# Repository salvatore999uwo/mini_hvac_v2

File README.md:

# mini_hvac_v2
Second version of the temperature control system for a small model room.

Photos:
As shown below, this version is made from three parts: Wooden structure, electronic boards, and thermal transfer area. 
The wooden structure is made up of a plywood base and a model room built from studs. There will be a drywall covering over the stud room to simulate a real temperature-controlled room.
The electronic boards are simply the PCB and the power supply for the project. There will be several wires running between the boards and the thermal transfer area.
The thermal transfer area is shown by the heatsinks and fans on the picture below. This area is composed of the TEC module, which creates a large temperature difference, and the heatsinks and fans that allow the TEC module to move thermal energy out of or into the room.

Current PCB 3D Model:

One schematic page i've been working on:

Current PCB Design:

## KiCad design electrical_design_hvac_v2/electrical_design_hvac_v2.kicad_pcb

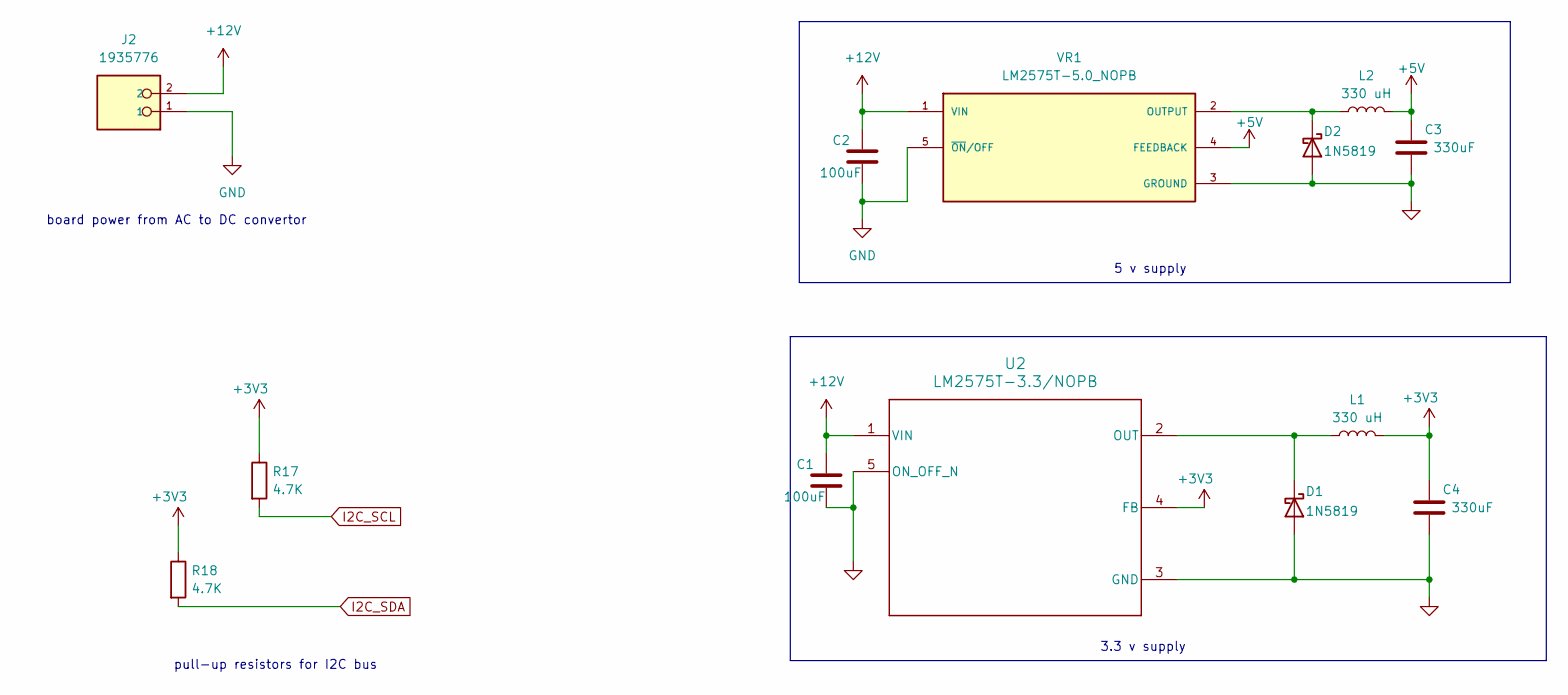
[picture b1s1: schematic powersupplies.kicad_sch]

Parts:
C1, C2: 100uF; C_1210_3225Metric_Pad1.33x2.70mm_HandSolder
C3, C4: 330uF; C_1210_3225Metric_Pad1.33x2.70mm_HandSolder
D1, D2: 1N5819; D_DO-41_SOD81_P10.16mm_Horizontal
J2: 1935776; PHOENIX_1935776; PARTREV 19.10.2016
L1, L2: 330 uH; IND_1210-WE-PD_WRE
R17, R18: 4.7K; R_1210_3225Metric_Pad1.30x2.65mm_HandSolder
U2: LM2575T-3.3/NOPB; KC0005A
VR1: LM2575T-5.0_NOPB; KC0005A; PARTREV E

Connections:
+5V: C3.1, L2.2, VR1.4 (FEEDBACK); also elsewhere on the board
+12V: C1.1, C2.1, J2.2, U2.1 (VIN), VR1.1 (VIN); also elsewhere on the board
GND: C1.2, C2.2, C3.2, C4.2, D1.2 (A), D2.2 (A), J2.1, U2.3 (GND), U2.5 (ON_OFF_N), VR1.3 (GROUND), VR1.5 (~ON/OFF); also elsewhere on the board
I2C_SCL: R17.2; also elsewhere on the board
I2C_SDA: R18.2; also elsewhere on the board
unnamed: D1.1 (K), L1.1, U2.2 (OUT)
unnamed: D2.1 (K), L2.1, VR1.2 (OUTPUT)

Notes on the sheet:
5 v supply
board power from AC to DC convertor
pull-up resistors for I2C bus
3.3 v supply

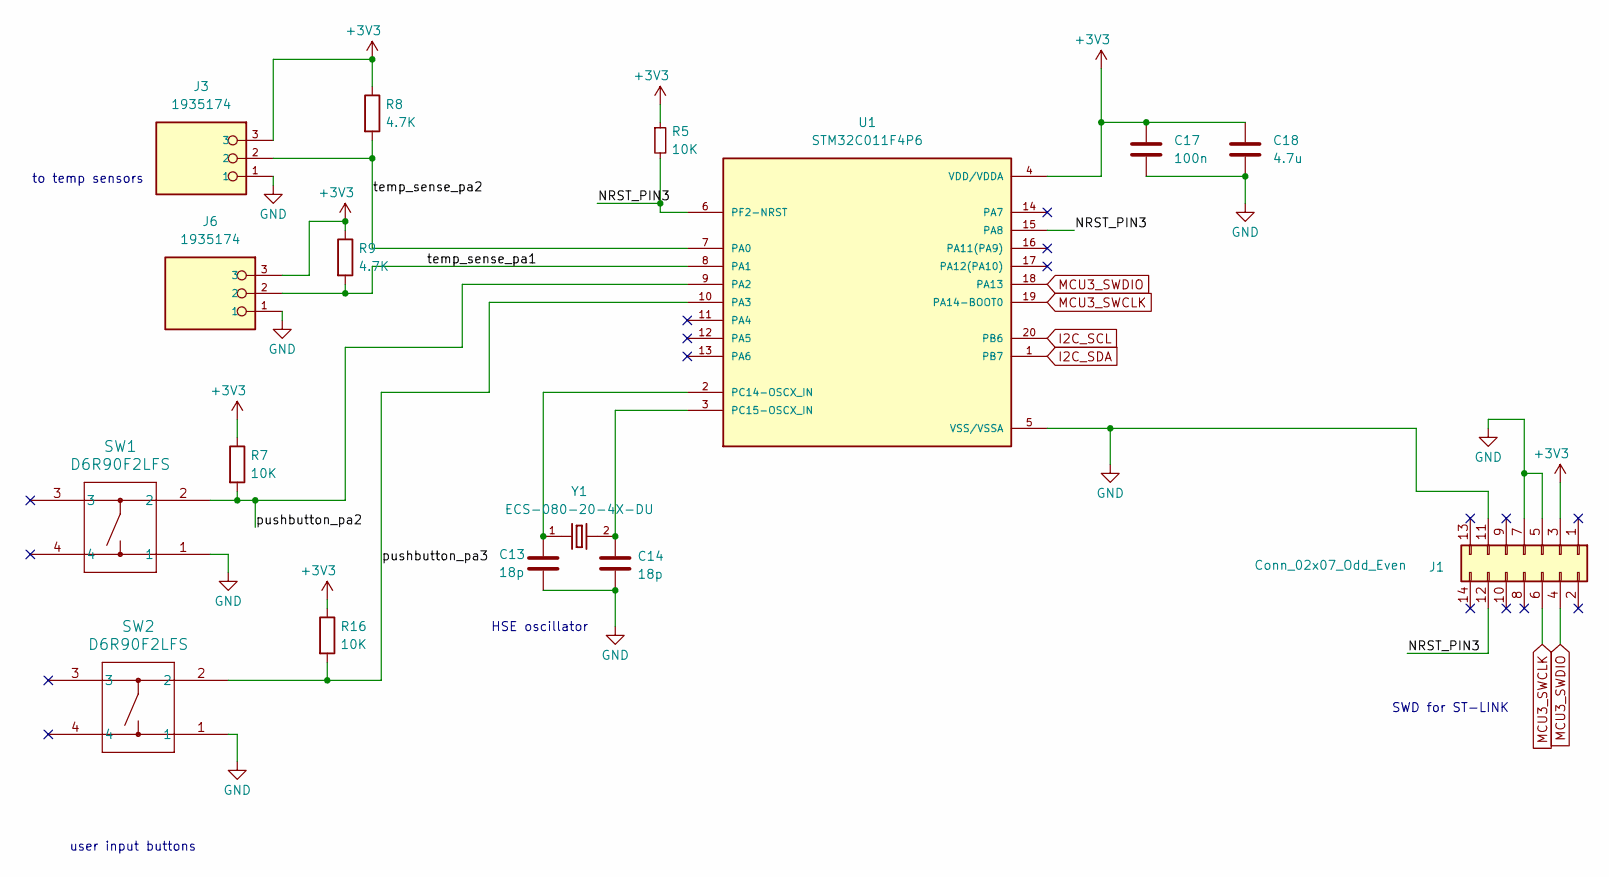
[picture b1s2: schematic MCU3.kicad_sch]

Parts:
C13, C14: 18p; C_1210_3225Metric_Pad1.33x2.70mm_HandSolder
C17: 100n; C_1210_3225Metric_Pad1.33x2.70mm_HandSolder
C18: 4.7u; C_1210_3225Metric_Pad1.33x2.70mm_HandSolder
J1: Conn_02x07_Odd_Even; PinHeader_2x07_P1.27mm_Vertical
J3, J6: 1935174; PHOENIX_1935174
R5, R7, R16: 10K; R_1210_3225Metric_Pad1.30x2.65mm_HandSolder
R8, R9: 4.7K; R_1210_3225Metric_Pad1.30x2.65mm_HandSolder
SW1, SW2: D6R90F2LFS; D6R90_CNK
U1: STM32C011F4P6; SOP65P640X120-20N; PARTREV 3
Y1: ECS-080-20-4X-DU; XTAL_ECS-160-20-4X

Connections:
/MCU3/NRST_PIN3: J1.12, R5.2, U1.6 (PF2-NRST), U1.15 (PA8)
/MCU3/pushbutton_pa2: R7.2, SW1.2, U1.9 (PA2)
/MCU3/pushbutton_pa3: R16.2, SW2.2, U1.10 (PA3)
/MCU3/temp_sense_pa1: J6.2, R9.2, U1.8 (PA1)
/MCU3/temp_sense_pa2: J3.2, R8.2, U1.7 (PA0)
GND: C13.2, C14.2, C17.2, C18.2, J1.5, J1.7, J1.11, J3.1, J6.1, SW1.1, SW2.1, U1.5 (VSS/VSSA); also elsewhere on the board
I2C_SCL: U1.20 (PB6); also elsewhere on the board
I2C_SDA: U1.1 (PB7); also elsewhere on the board
MCU3_SWCLK: J1.6, U1.19 (PA14-BOOT0)
MCU3_SWDIO: J1.4, U1.18 (PA13)
unnamed: C13.1, U1.2 (PC14-OSCX_IN), Y1.1
unnamed: C14.1, U1.3 (PC15-OSCX_IN), Y1.2

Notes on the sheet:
HSE oscillator
user input buttons
SWD for ST-LINK
to temp sensors

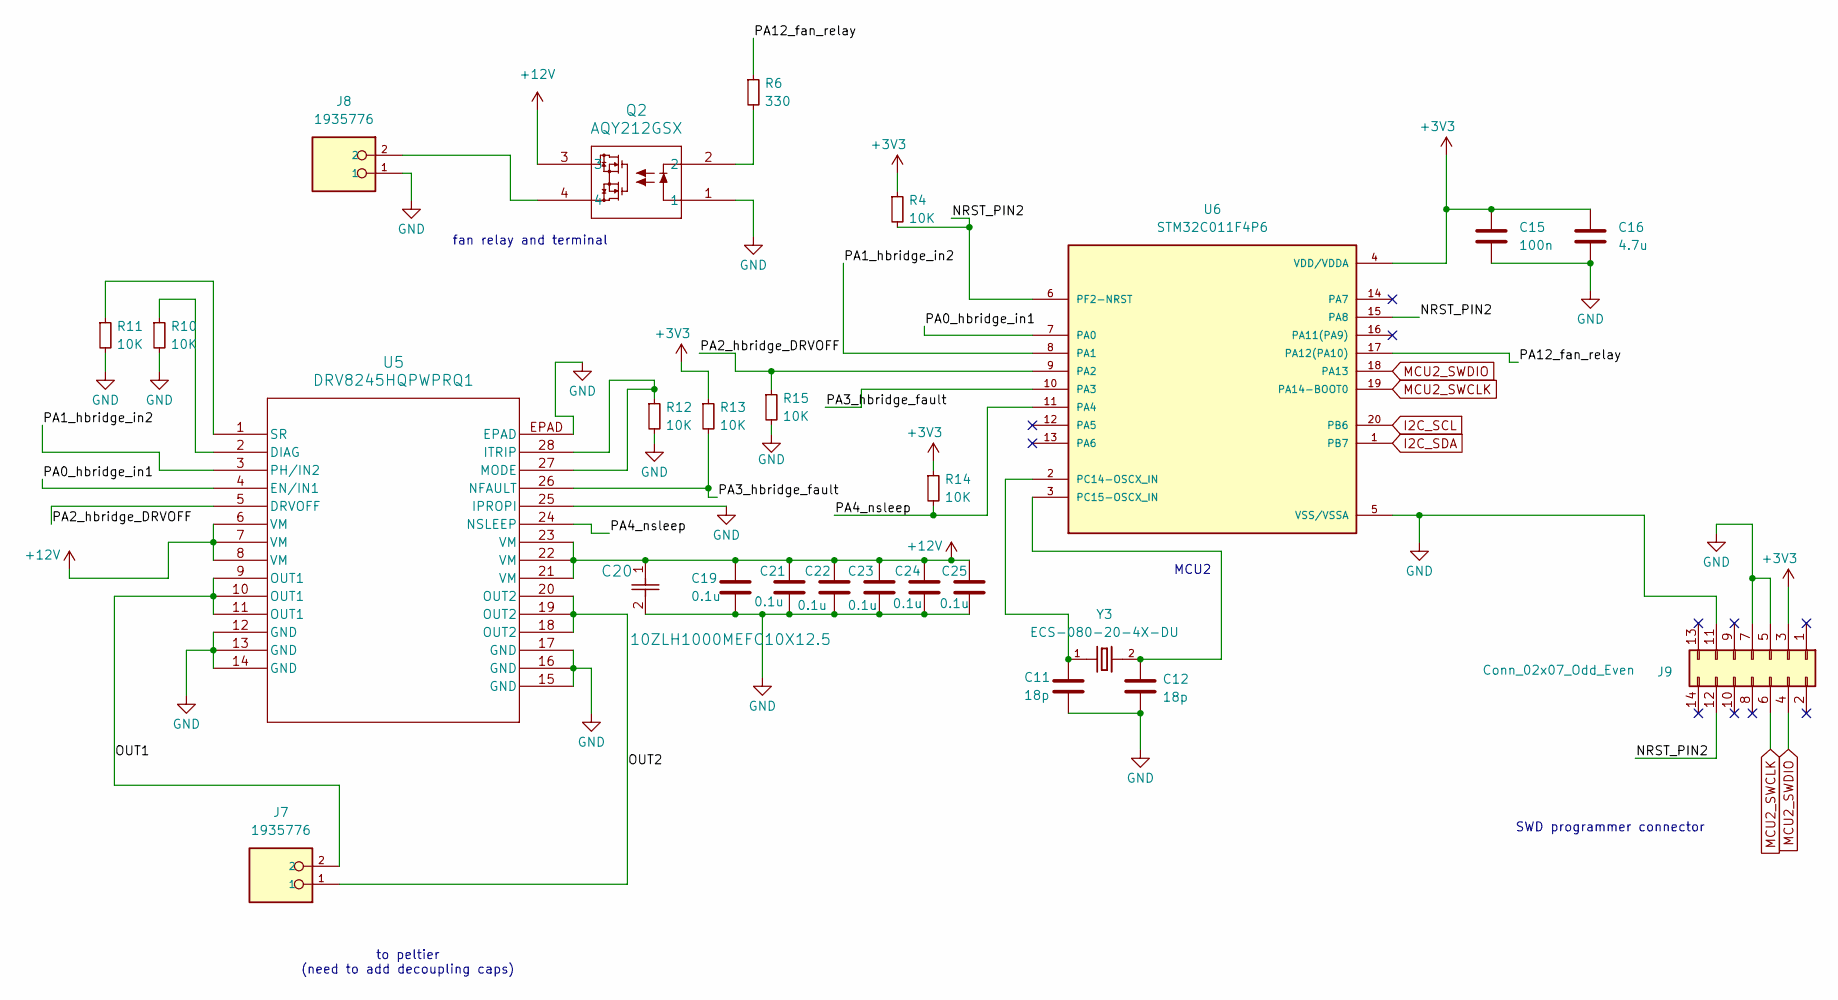
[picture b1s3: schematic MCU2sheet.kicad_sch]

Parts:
C11, C12: 18p; C_1210_3225Metric_Pad1.33x2.70mm_HandSolder
C15: 100n; C_1210_3225Metric_Pad1.33x2.70mm_HandSolder
C16: 4.7u; C_1210_3225Metric_Pad1.33x2.70mm_HandSolder
C19, C21, C22, C23, C24, C25: 0.1u; C_1210_3225Metric_Pad1.33x2.70mm_HandSolder
C20: 10ZLH1000MEFC10X12.5; CAP_10X12.5_RUB
J7, J8: 1935776; PHOENIX_1935776; PARTREV 19.10.2016
J9: Conn_02x07_Odd_Even; PinHeader_2x07_P1.27mm_Vertical
Q2: AQY212GSX; SOP4_PAN
R4, R10, R11, R12, R13, R14, R15: 10K; R_1210_3225Metric_Pad1.30x2.65mm_HandSolder
R6: 330; R_1210_3225Metric_Pad1.30x2.65mm_HandSolder
U5: DRV8245HQPWPRQ1; HTSSOP28_PWP_TEX
U6: STM32C011F4P6; SOP65P640X120-20N; PARTREV 3
Y3: ECS-080-20-4X-DU; XTAL_ECS-160-20-4X

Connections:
+12V: C19.1, C20.1, C21.1, C22.1, C23.1, C24.1, C25.1, Q2.3, U5.6 (VM), U5.7 (VM), U5.8 (VM), U5.21 (VM), U5.22 (VM), U5.23 (VM); also elsewhere on the board
/MCU2/NRST_PIN2: J9.12, R4.2, U6.6 (PF2-NRST), U6.15 (PA8)
/MCU2/OUT1: J7.2, U5.9 (OUT1), U5.10 (OUT1), U5.11 (OUT1)
/MCU2/OUT2: J7.1, U5.18 (OUT2), U5.19 (OUT2), U5.20 (OUT2)
/MCU2/PA0_hbridge_in1: U5.4 (EN/IN1), U6.7 (PA0)
/MCU2/PA1_hbridge_in2: U5.3 (PH/IN2), U6.8 (PA1)
/MCU2/PA2_hbridge_DRVOFF: R15.1, U5.5 (DRVOFF), U6.9 (PA2)
/MCU2/PA3_hbridge_fault: R13.2, U5.26 (NFAULT), U6.10 (PA3)
/MCU2/PA4_nsleep: R14.2, U5.24 (NSLEEP), U6.11 (PA4)
/MCU2/PA12_fan_relay: R6.1, U6.17 (PA12(PA10))
GND: C11.2, C12.2, C15.2, C16.2, C19.2, C20.2, C21.2, C22.2, C23.2, C24.2, C25.2, J8.1, J9.5, J9.7, J9.11, Q2.1, R10.2, R11.2, R12.2, R15.2, U5.12 (GND), U5.13 (GND), U5.14 (GND), U5.15 (GND), U5.16 (GND), U5.17 (GND), U5.25 (IPROPI), U5.EPAD, U6.5 (VSS/VSSA); also elsewhere on the board
I2C_SCL: U6.20 (PB6); also elsewhere on the board
I2C_SDA: U6.1 (PB7); also elsewhere on the board
MCU2_SWCLK: J9.6, U6.19 (PA14-BOOT0)
MCU2_SWDIO: J9.4, U6.18 (PA13)
unnamed: J8.2, Q2.4
unnamed: Q2.2, R6.2
unnamed: R10.1, U5.2 (DIAG)
unnamed: R12.1, U5.27 (MODE), U5.28 (ITRIP)
unnamed: R11.1, U5.1 (SR)
unnamed: C11.1, U6.2 (PC14-OSCX_IN), Y3.1
unnamed: C12.1, U6.3 (PC15-OSCX_IN), Y3.2

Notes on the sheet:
to peltier (need to add decoupling caps)
fan relay and terminal
MCU2
SWD programmer connector

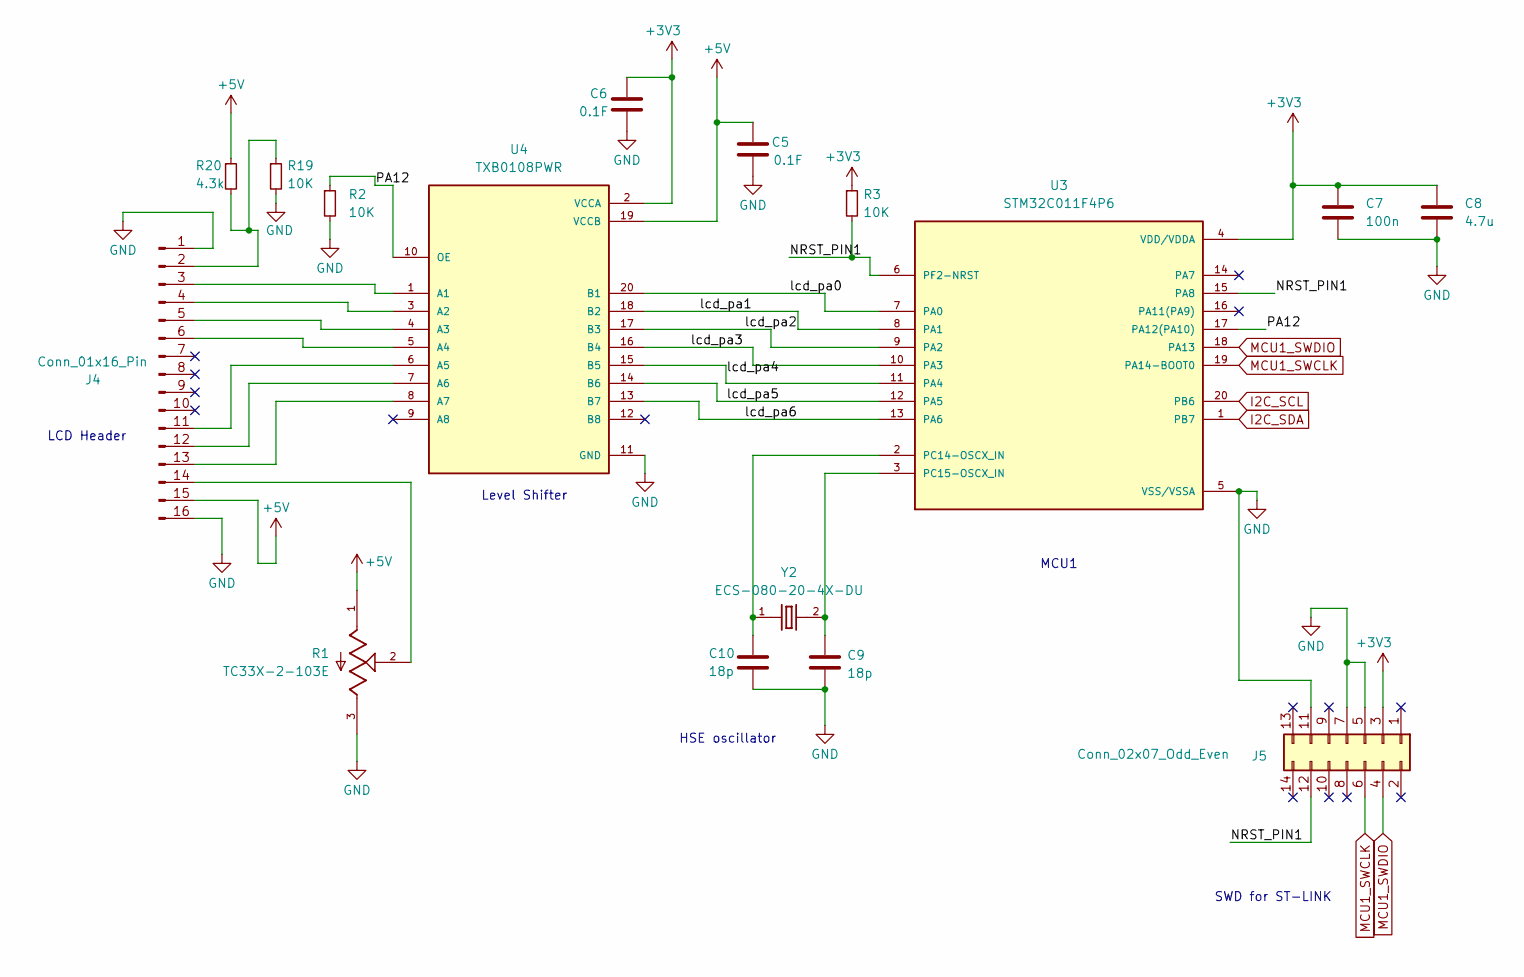
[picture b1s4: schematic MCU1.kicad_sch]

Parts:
C5, C6: 0.1F; C_1210_3225Metric_Pad1.33x2.70mm_HandSolder
C7: 100n; C_1210_3225Metric_Pad1.33x2.70mm_HandSolder
C8: 4.7u; C_1210_3225Metric_Pad1.33x2.70mm_HandSolder
C9, C10: 18p; C_1210_3225Metric_Pad1.33x2.70mm_HandSolder
J4: Conn_01x16_Pin; PinHeader_1x16_P1.27mm_Vertical
J5: Conn_02x07_Odd_Even; PinHeader_2x07_P1.27mm_Vertical
R1: TC33X-2-103E; TRIM_TC33X-2-103E
R2, R3, R19: 10K; R_1210_3225Metric_Pad1.30x2.65mm_HandSolder
R20: 4.3k; R_1210_3225Metric_Pad1.30x2.65mm_HandSolder
U3: STM32C011F4P6; SOP65P640X120-20N; PARTREV 3
U4: TXB0108PWR; SOP65P640X120-20N; PARTREV H
Y2: ECS-080-20-4X-DU; XTAL_ECS-160-20-4X

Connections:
+5V: C5.1, J4.15, R1.1, R20.1, U4.19 (VCCB); also elsewhere on the board
/MCU1/NRST_PIN1: J5.12, R3.2, U3.6 (PF2-NRST), U3.15 (PA8)
/MCU1/PA12: R2.1, U3.17 (PA12(PA10)), U4.10 (OE)
/MCU1/lcd_pa0: U3.7 (PA0), U4.20 (B1)
/MCU1/lcd_pa1: U3.8 (PA1), U4.18 (B2)
/MCU1/lcd_pa2: U3.9 (PA2), U4.17 (B3)
/MCU1/lcd_pa3: U3.10 (PA3), U4.16 (B4)
/MCU1/lcd_pa4: U3.11 (PA4), U4.15 (B5)
/MCU1/lcd_pa5: U3.12 (PA5), U4.14 (B6)
/MCU1/lcd_pa6: U3.13 (PA6), U4.13 (B7)
GND: C5.2, C6.2, C7.2, C8.2, C9.2, C10.2, J4.1, J4.16, J5.5, J5.7, J5.11, R1.3, R2.2, R19.2, U3.5 (VSS/VSSA), U4.11 (GND); also elsewhere on the board
I2C_SCL: U3.20 (PB6); also elsewhere on the board
I2C_SDA: U3.1 (PB7); also elsewhere on the board
MCU1_SWCLK: J5.6, U3.19 (PA14-BOOT0)
MCU1_SWDIO: J5.4, U3.18 (PA13)
unnamed: J4.2, R19.1, R20.2
unnamed: J4.3, U4.1 (A1)
unnamed: J4.4, U4.3 (A2)
unnamed: J4.5, U4.4 (A3)
unnamed: J4.6, U4.5 (A4)
unnamed: J4.11, U4.6 (A5)
unnamed: J4.12, U4.7 (A6)
unnamed: J4.13, U4.8 (A7)
unnamed: J4.14, R1.2
unnamed: C10.1, U3.2 (PC14-OSCX_IN), Y2.1
unnamed: C9.1, U3.3 (PC15-OSCX_IN), Y2.2

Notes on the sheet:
Level Shifter
MCU1
LCD Header
HSE oscillator
SWD for ST-LINK

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
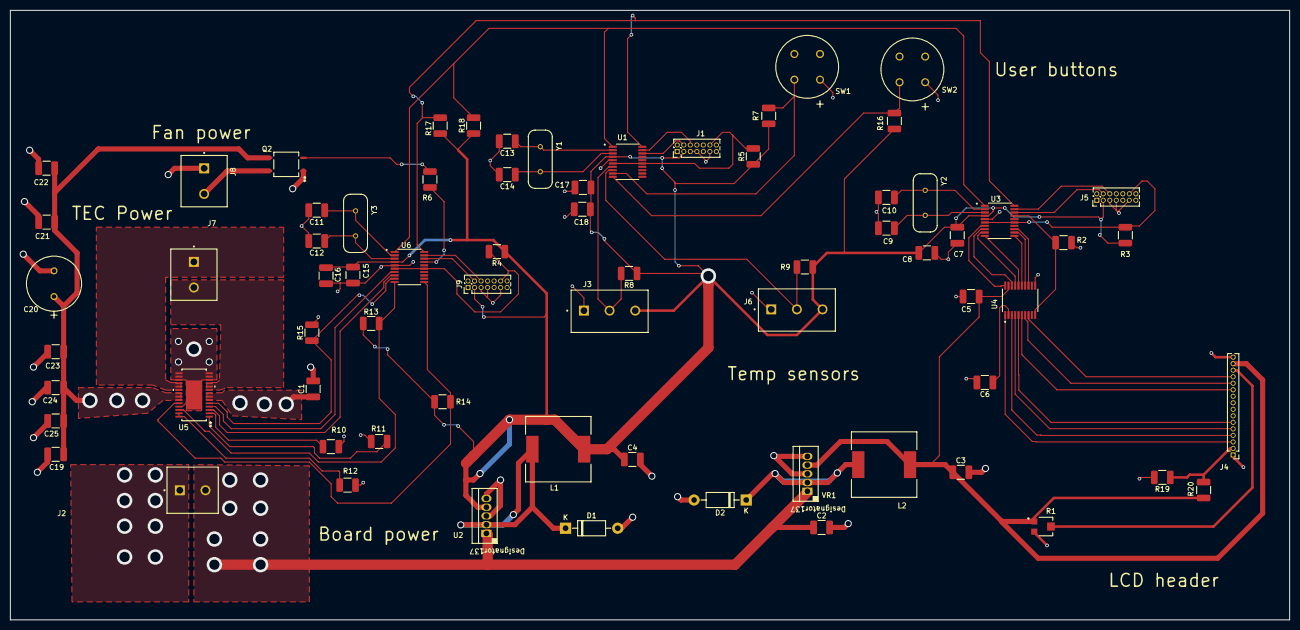
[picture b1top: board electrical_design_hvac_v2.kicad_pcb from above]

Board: 2 copper layers, 249.2 x 118.8 mm, 71 parts (0 on the bottom side), 58 nets.

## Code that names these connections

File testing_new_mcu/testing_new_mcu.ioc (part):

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Mcu.Name=STM32C011F(4-6)Px
Mcu.Package=TSSOP20
Mcu.UserName=STM32C011F4Px
PA13.Mode=Serial_Wire
PA13.Signal=DEBUG_SWDIO
PA14-BOOT0.Mode=Serial_Wire
PA14-BOOT0.Signal=DEBUG_SWCLK
PB6.Mode=I2C
PB6.Signal=I2C1_SCL
PB7.Mode=I2C
PB7.Signal=I2C1_SDA
RCC.HSE_VALUE=8000000
RCC.SYSCLKFreq_VALUE=12000000
board=custom

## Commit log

2024-07-16 Create todo
2024-07-17 new electrical schematics
2024-07-17 Add files via upload
    keeping these symbol files for the electrical design
2024-07-19 Add files via upload
    new photo of pcb
2024-07-31 Add files via upload
    first version of software
